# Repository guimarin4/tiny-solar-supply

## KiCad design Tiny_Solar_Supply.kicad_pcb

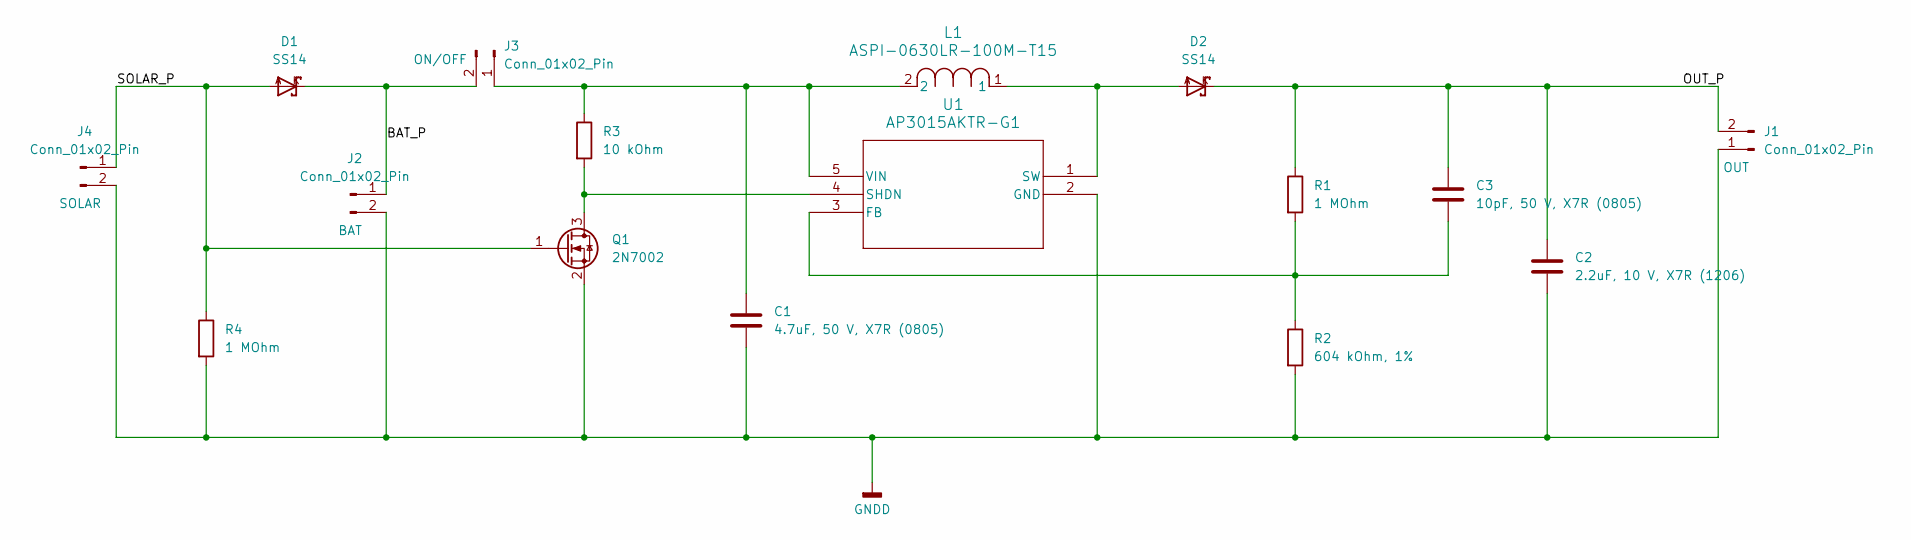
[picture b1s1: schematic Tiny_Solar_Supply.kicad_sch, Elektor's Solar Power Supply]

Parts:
C1: 4.7uF, 50 V, X7R (0805); C_0805_2012Metric
C2: 2.2uF, 10 V, X7R (1206); C_1206_3216Metric
C3: 10pF, 50 V, X7R (0805); C_0805_2012Metric
D1, D2: SS14; DO-214AC
J1, J2, J3: Conn_01x02_Pin; PinHeader_1x02_P2.54mm_Vertical
J4: Conn_01x02_Pin; PinHeader_1x02_P2.54mm_Horizontal
L1: ASPI-0630LR-100M-T15; IND_ASPI-0630LR_ABR
Q1: 2N7002; SOT-23
R1, R4: 1 MOhm; R_0805_2012Metric
R2: 604 kOhm, 1%; R_0805_2012Metric
R3: 10 kOhm; R_0805_2012Metric
U1: AP3015AKTR-G1; SOT23-5_1P55X2P9_DIO

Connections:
/BAT_P: D1.K, J2.1, J3.2
/OUT_P: C2.1, C3.1, D2.K, J1.2, R1.1
/SOLAR_P: D1.A, J4.1, Q1.1 (G), R4.1
GNDD: C1.2, C2.2, J1.1, J2.2, J4.2, Q1.2 (S), R2.2, R4.2, U1.2 (GND)
unnamed: C1.1, J3.1, L1.2, R3.1, U1.5 (VIN)
unnamed: Q1.3 (D), R3.2, U1.4 (SHDN)
unnamed: C3.2, R1.2, R2.1, U1.3 (FB)
unnamed: D2.A, L1.1, U1.1 (SW)

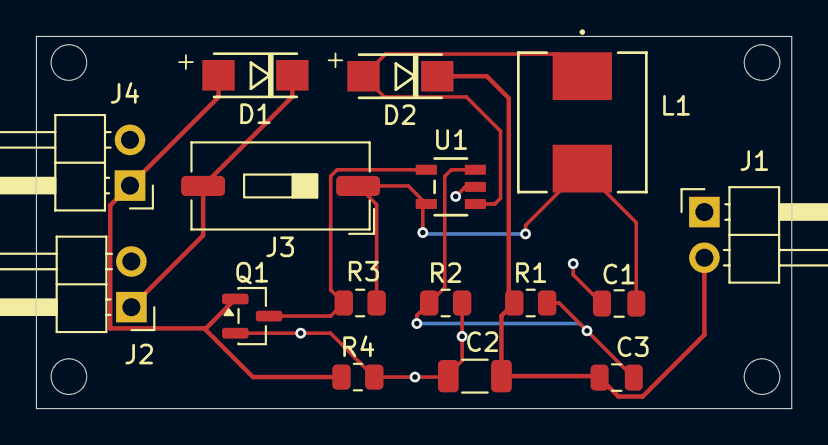
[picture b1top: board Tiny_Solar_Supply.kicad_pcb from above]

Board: 2 copper layers, 42.0 x 20.7 mm, 16 parts (0 on the bottom side), 8 nets.
